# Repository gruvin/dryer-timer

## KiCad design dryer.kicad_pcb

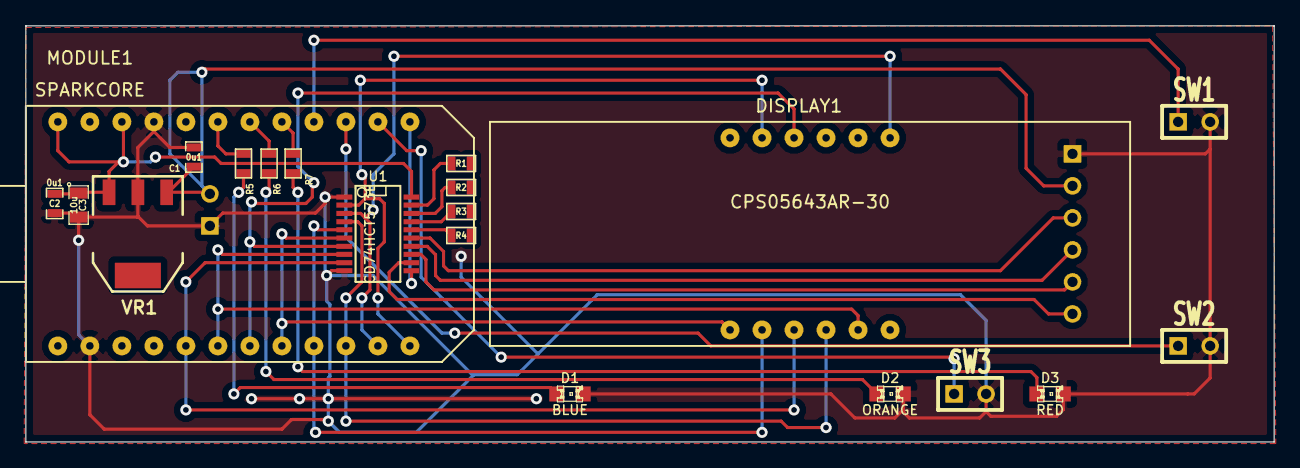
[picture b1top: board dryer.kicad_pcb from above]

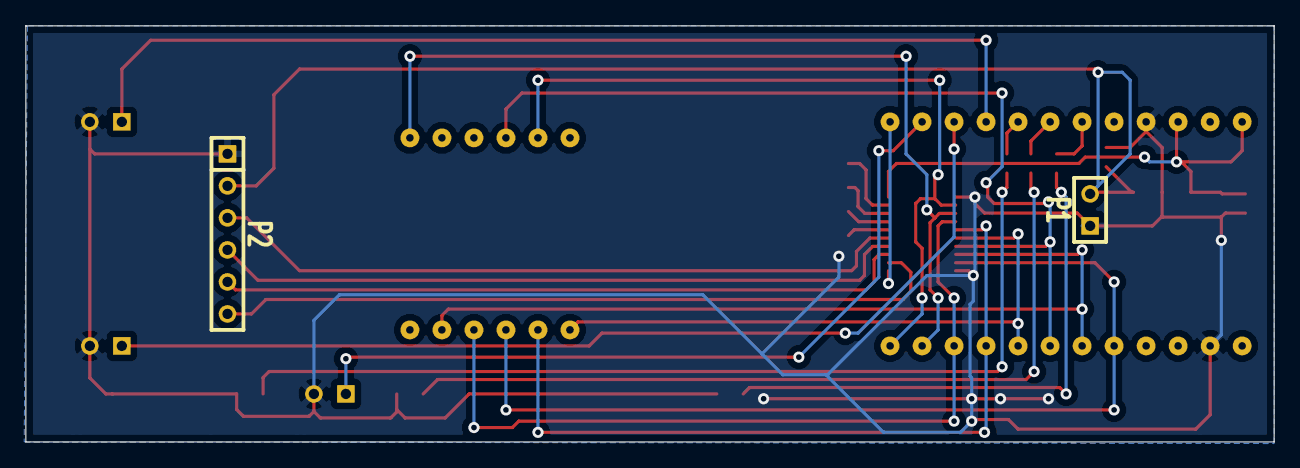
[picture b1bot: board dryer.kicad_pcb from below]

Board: 2 copper layers, 99.1 x 33.0 mm, 22 parts (2 on the bottom side), 29 nets.

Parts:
C1, C2: 0u1; SM0603_Capa
C3: 10u; SM0805
D1: BLUE; LED-0805
D2: ORANGE; LED-0805
D3: RED; LED-0805
DISPLAY1: CPS05643AR-30; LED-7SEG-4DIGIT
MODULE1: SPARKCORE
P1: CONN_2; SIL-2
P2: CONN_6; SIL-6
R1, R2, R3, R4: 5K1; SM0603
R5, R6, R7: 680; SM0603
SW1: TEMP SELECT; SIL-2
SW2: TIME DOWN; SIL-2
SW3: TIME UP / START; SIL-2
U1: CD74HCT573E; SSOP20
VR1: UA78M33CDCY; SOT223

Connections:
+5V: C1.1, P1.2, P2.2, VR1.1
/RLY_HEAT1: P2.5, U1.13
/RLY_HEAT2: P2.6, U1.12
/RLY_PWR1: P2.3, U1.15
/RLY_PWR2: P2.4, U1.14
GND: C1.2, C2.2, C3.2, D1.2, D2.2, D3.2, MODULE1.2, MODULE1.21, P1.1, P2.1, SW1.2, SW2.2, SW3.2, U1.1, U1.10, VR1.2
unnamed: MODULE1.19, R5.1
unnamed: MODULE1.18, R6.1
unnamed: DISPLAY1.11, MODULE1.12, U1.2
unnamed: MODULE1.16, SW1.1
unnamed: MODULE1.17, R7.1
unnamed: MODULE1.14, SW3.1
unnamed: MODULE1.15, SW2.1
unnamed: MODULE1.13, U1.11
unnamed: R2.1, U1.18
unnamed: R4.1, U1.16
unnamed: R3.1, U1.17
unnamed: R1.1, U1.19
unnamed: D2.1, R6.2
unnamed: D3.1, R7.2
unnamed: D1.1, R5.2
unnamed: DISPLAY1.7, MODULE1.11, U1.3
unnamed: DISPLAY1.4, MODULE1.10, U1.4
unnamed: DISPLAY1.2, MODULE1.9, U1.5
unnamed: DISPLAY1.1, MODULE1.8, U1.6
unnamed: DISPLAY1.10, MODULE1.7, U1.7
unnamed: DISPLAY1.5, MODULE1.6, U1.8
unnamed: DISPLAY1.3, MODULE1.5, U1.9
VCC: C2.1, C3.1, MODULE1.22, MODULE1.24, U1.20, VR1.3

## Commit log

2024-12-17 Very old code / design circa 2011(ish)
